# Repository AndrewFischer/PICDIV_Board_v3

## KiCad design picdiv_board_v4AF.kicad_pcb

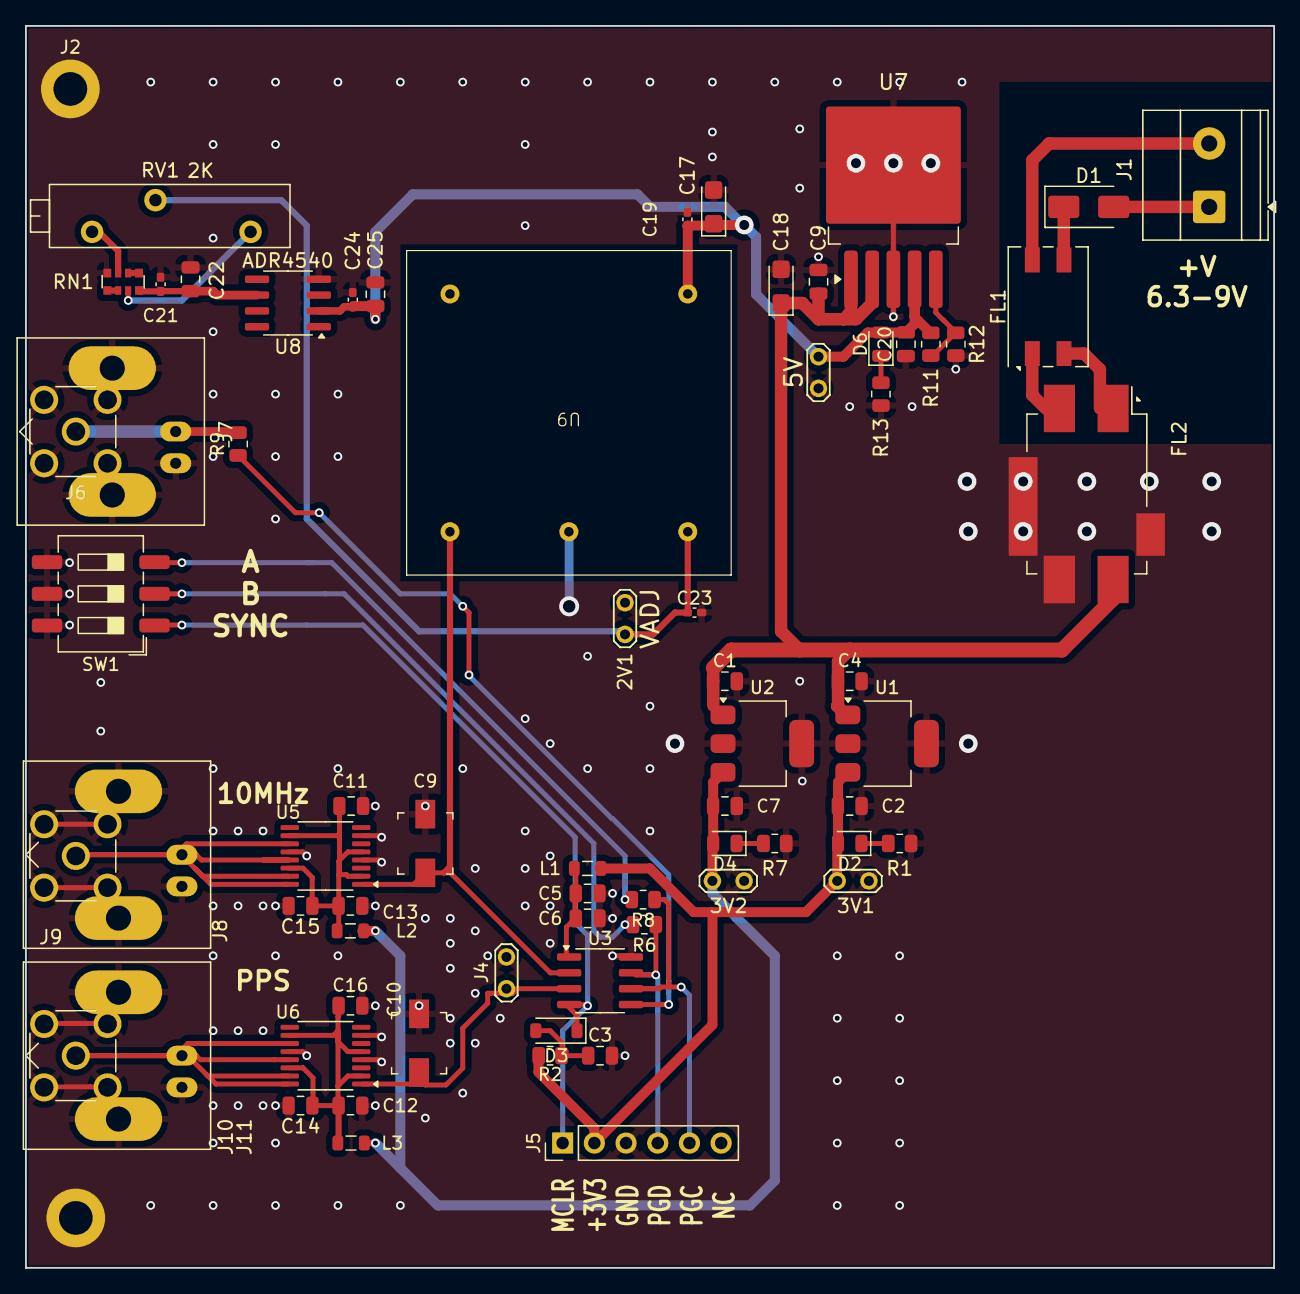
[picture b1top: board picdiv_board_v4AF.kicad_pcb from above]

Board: 2 copper layers, 100.0 x 99.5 mm, 70 parts (0 on the bottom side), 35 nets.

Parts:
2V1: VADJ; TestPoint_2Pads_Pitch2.54mm_Drill0.8mm
3V1, 3V2: TEST_3V3; TestPoint_2Pads_Pitch2.54mm_Drill0.8mm
5V1: 5V; TestPoint_2Pads_Pitch2.54mm_Drill0.8mm
C1, C2, C4, C5, C7, C9: 10u; C_0805_2012Metric
C3, C6, C11, C12, C13, C14, C15, C16: 100n; C_0805_2012Metric
C9#2, C10: C_Trim; C_Trimmer_Murata_TZB4-A
C17, C18: 10µF; CP_EIA-3216-18_Kemet-A
C19, C21, C23, C24: 100nF; C_0402_1005Metric_Pad0.74x0.62mm_HandSolder
C20, C22, C25: 10µF; C_0805_2012Metric
D1: SS34; D_SMA
D2, D4, D6: LED; LED_0805_2012Metric
D3: 1N4148W; D_SOD-123
FL1: Filter_EMI_LL_1423; Filter_Bourns_SRF0905_6.0x9.2mm
FL2: BNX025; Filter_Murata_BNX025
J1: DC-Input; TerminalBlock_Phoenix_MKDS-1,5-2-5.08_1x02_P5.08mm_Horizont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
J2, J3: MountingHole_M2.5; MountingHole_2.7mm_M2.5_DIN965_Pad
J4: TEST_1PPS; TestPoint_2Pads_Pitch2.54mm_Drill0.8mm
J5: Conn_01x06; PinHeader_1x06_P2.54mm_Vertical
J6: Sync; SMA_Molex_73251-2200_Horizontal
J7: Sync; BNC_Amphenol_B6252HB-NPP3G-50_Horizontal
J8: 10MHz; BNC_Amphenol_B6252HB-NPP3G-50_Horizontal
J9: 10MHz; SMA_Molex_73251-2200_Horizontal
J10: PPS_B; BNC_Amphenol_B6252HB-NPP3G-50_Horizontal
J11: PPS_B; SMA_Molex_73251-2200_Horizontal
L1, L2, L3: 2u2; L_0805_2012Metric
R1, R7: 100Ω; R_0805_2012Metric
R2: 3k3; R_0805_2012Metric
R6, R8: 10k; R_0805_2012Metric
R9: 50; R_0805_2012Metric
R11: 2k15; R_0805_2012Metric
R12: 680R; R_0805_2012Metric
R13: 330R; R_0805_2012Metric
RN1: 1K 0.1% ±15ppm; R_Array_Convex_4x0612
RV1: 2K; Potentiometer_Bourns_3006P_Horizontal
SW1: SW_DIP_x03; SW_DIP_SPSTx03_Slide_6.7x9.18mm_W8.61mm_P2.54mm_LowProfile
U1, U2: LT1963AEST-3.3; SOT-223-3_TabPin2
U3: PIC12F675-xSN; SOIC-8_3.9x4.9mm_P1.27mm
U5, U6: IDT5PB1108; TSSOP-16_4.4x5mm_P0.65mm
U7: LT1963AEQ; TO-263-5_TabPin3
U8: ADR4540; SOIC-8_3.9x4.9mm_P1.27mm
U9: OSC5A2B02

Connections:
3V3_OUT: 3V2.1, C7.1, D4.2 (A), L2.2, L3.2, U2.3 (OUT)
3V3_PIC: 3V1.1, C2.1, D2.2 (A), J5.2, L1.2, R2.1, U1.3 (OUT)
10MHz: C9#2.2, U3.2 (GP5), U5.1 (CLKIN), U9.1 (Out)
+5V: 5V1.1, C17.1, C19.1, C20.2, C24.1, C25.1, D6.2 (A), R11.1, U7.4 (OUT), U8.2 (IN), U9.5 (Vcc)
/A: R8.2, SW1.3
/B: R6.2, SW1.2
/PPS_B: J10.1 (In), J11.1 (In), U6.11 (Y5), U6.13 (Y2), U6.15 (Y3), U6.16 (Y1)
/U6_3V3: C12.1, C14.1, C16.1, L3.1, U6.2 (1G), U6.5 (VDD), U6.10 (VDD), U6.14 (VDD)
/U105_3V3: C11.1, C13.1, C15.1, L2.1, U5.2 (1G), U5.5 (VDD), U5.10 (VDD), U5.14 (VDD)
/sync: R9.1, U3.5 (GP2)
/w1: D1.2 (A), J1.1
/w2: D1.1 (K), FL1.3
/w3: FL1.2, FL2.1 (B)
/w4: FL1.4, J1.2
/w5: FL1.1, FL2.3 (PSG)
GND: 2V1.2, 3V1.2, 3V2.2, 5V1.2, C1.2, C2.2, C3.2, C4.2, C5.2, C6.2, C7.2, C9.2, C9#2.1, C10.2, C11.2, C12.2, C13.2, C14.2, C15.2, C16.2, C17.2, C18.2, C19.2, C20.1, C21.2, C22.2, C23.2, C24.2, C25.2, FL2.4 (CG), J2.1, J3.1, J4.2, J5.3, J6.2 (Ext), J7.2 (Ext), J8.2 (Ext), J9.2 (Ext), J10.2 (Ext), J11.2 (Ext), R1.1, R7.1, R12.2, R13.2, RN1.4 (R4.1), SW1.4, SW1.5, SW1.6, U1.2 (GND), U2.2 (GND), U3.8 (VSS), U5.4 (GND), U5.7 (GND), U5.12 (GND), U6.4 (GND), U6.7 (GND), U6.12 (GND), U7.3 (GND), U8.4 (GND), U9.2 (GND)
LDO_IN: C1.1, C4.1, C9.1, C18.1, FL2.2 (CB), U1.1 (IN), U2.1 (IN), U7.1 (~SHDN), U7.2 (IN)
MCLR: D3.1 (K), J5.1, SW1.1, U3.4 (GP3)
unnamed: D2.1 (K), R1.2
unnamed: C3.1, D3.2 (A), R2.2
unnamed: D4.1 (K), R7.2
unnamed: D6.1 (K), R13.1
unnamed: J6.1 (In), J7.1 (In), R9.2
unnamed: J8.1 (In), J9.1 (In), U5.11 (Y5), U5.13 (Y2), U5.15 (Y3), U5.16 (Y1)
unnamed: RN1.1 (R1.1), RN1.2 (R2.1)
unnamed: C21.1, C22.1, RN1.8 (R1.2), U8.6 (OUT)
unnamed: RN1.7 (R2.2), RV1.1
unnamed: RN1.3 (R3.1), RV1.3
unnamed: RN1.5 (R4.2), RN1.6 (R3.2)
unnamed: C5.1, C6.1, L1.1, U3.1 (VDD)
unnamed: R11.2, R12.1, U7.5 (ADJ)
PGC: J5.5, R8.1, U3.6 (GP1)
PGD: J5.4, R6.1, U3.7 (GP0)
PPS: C10.1, J4.1, U3.3 (GP4), U6.1 (CLKIN)
Vadj: 2V1.1, C23.1, RV1.2, U9.3 (Vref)

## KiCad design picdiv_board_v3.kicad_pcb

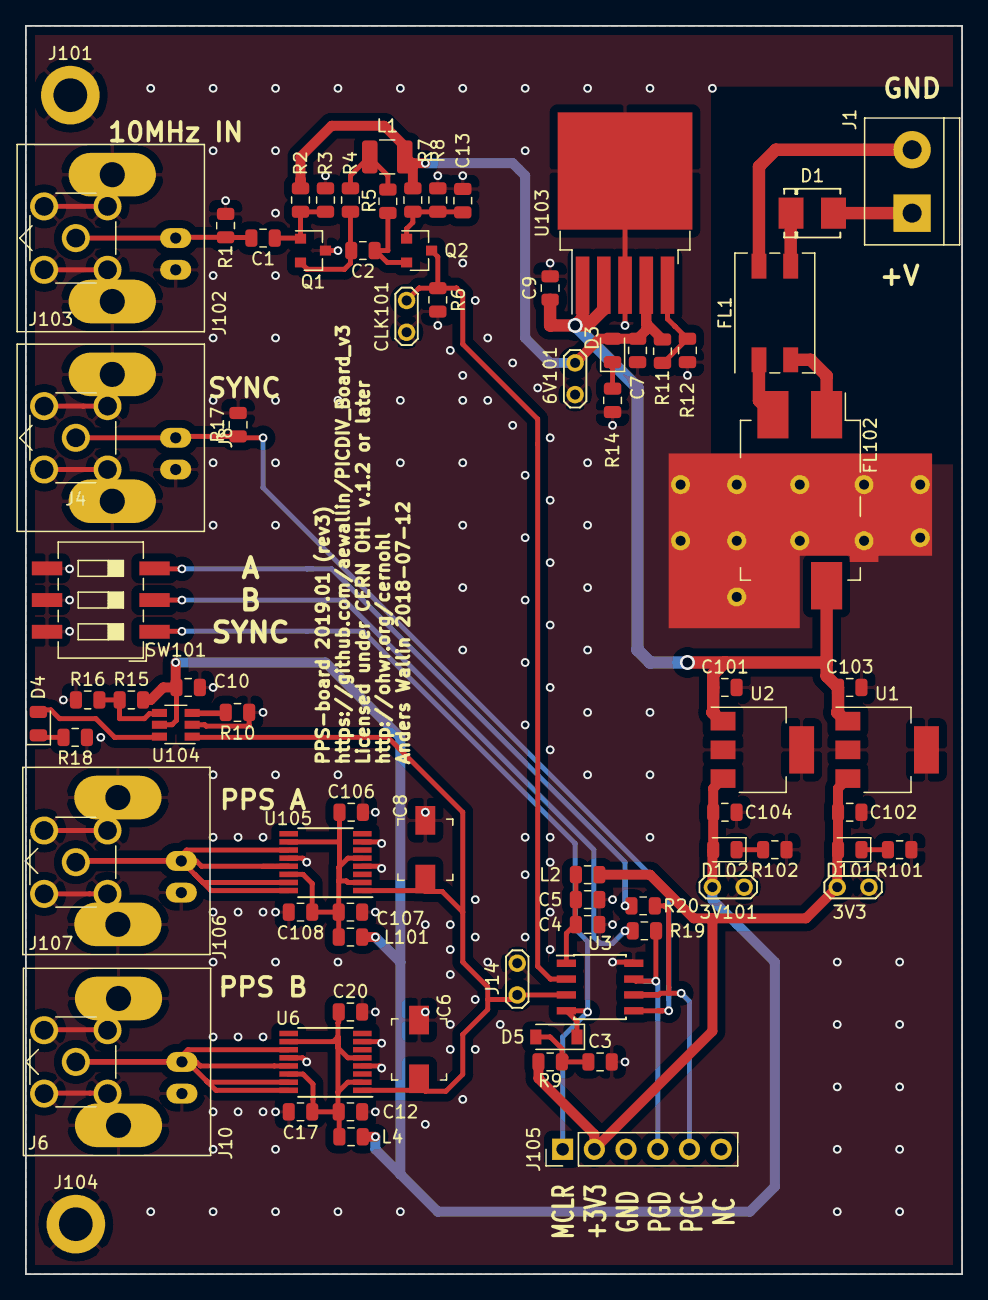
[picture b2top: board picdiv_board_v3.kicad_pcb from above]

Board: 2 copper layers, 75.0 x 100.0 mm, 81 parts (0 on the bottom side), 38 nets.

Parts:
3V3, 3V101: TEST_3V3; TestPoint_2Pads_Pitch2.54mm_Drill0.8mm
6V101: TEST_6V; TestPoint_2Pads_Pitch2.54mm_Drill0.8mm
C1, C13: 10n; C_0805_2012Metric
C2, C4, C12, C17, C20, C106, C107, C108: 100n; C_0805_2012Metric
C3, C10: C; C_0805_2012Metric
C5, C7, C9, C101, C102, C103, C104: 10u; C_0805_2012Metric
C6, C8: C_Trim; C_Trimmer_Murata_TZB4-A
CLK101: TEST_CLK; TestPoint_2Pads_Pitch2.54mm_Drill0.8mm
D1: D; DIODE_DO-214BA
D3, D101, D102: LED; LED_0805_2012Metric
D4: PPS_BLINK; LED_0805_2012Metric
D5: 1N4148; D_SOD-123
FL1: Filter_EMI_LL_1423; Filter_Bourns_SRF0905_6.0x9.2mm
FL102: BNX025; Filter_Murata_BNX025_ThermalVias
J1: DC-Input; TerminalBlock_bornier-2_P5.08mm
J4: SYNC; SMA_Molex_73251-2200_Horizontal
J6: PPS_B; SMA_Molex_73251-2200_Horizontal
J8: SYNC; BNC_Amphenol_B6252HB-NPP3G-50_Horizontal
J10: PPS_B; BNC_Amphenol_B6252HB-NPP3G-50_Horizontal
J14: TEST_1PPS; TestPoint_2Pads_Pitch2.54mm_Drill0.8mm
J101, J104: MountingHole_M2.5; MountingHole_2.7mm_M2.5_DIN965_Pad
J102: Conn_Coaxial; BNC_Amphenol_B6252HB-NPP3G-50_Horizontal
J103: Conn_Coaxial; SMA_Molex_73251-2200_Horizontal
J105: Conn_01x06; PinHeader_1x06_P2.54mm_Vertical
J106: PPS_A; BNC_Amphenol_B6252HB-NPP3G-50_Horizontal
J107: PPS_A; SMA_Molex_73251-2200_Horizontal
L1: 100u (1210); L_1210_3225Metric
L2, L4, L101: 2u2; L_0805_2012Metric
Q1, Q2: Q_PNP_BEC; SOT-23
R1: 49R9; R_0805_2012Metric
R2, R7, R9: 3k3; R_0805_2012Metric
R3, R8: 6k8; R_0805_2012Metric
R4, R5: 220R; R_0805_2012Metric
R6: 270R; R_0805_2012Metric
R10: 300k; R_0805_2012Metric
R11: 2k7; R_0805_2012Metric
R12: 680R; R_0805_2012Metric
R14: 200R; R_0805_2012Metric
R15: 1M; R_0805_2012Metric
R16: 523k; R_0805_2012Metric
R17: 50R; R_0805_2012Metric
R18: 100R; R_0805_2012Metric
R19, R20: 10k; R_0805_2012Metric
R101, R102: 82R; R_0805_2012Metric
SW101: SW_DIP_x03; SW_DIP_SPSTx03_Slide_6.7x9.18mm_W8.61mm_P2.54mm_LowProfile
U1, U2: LT1963AxST-3.3; SOT-223-3_TabPin2
U3: PIC12F675; SOIC-8_3.9x4.9mm_P1.27mm
U6, U105: IDT5PB1108; TSSOP-16_4.4x5mm_P0.65mm
U103: LT1963AEQ; TO-263-5_TabPin3
U104: LTC6993xS6-1; TSOT-23-6

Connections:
3V3_OUT: 3V101.1, C10.1, C104.1, D102.2, L4.2, L101.2, R15.2, U2.3, U104.5
3V3_PIC: 3V3.1, C102.1, D101.2, J105.2, L2.2, R9.1, U1.3
+6V: 6V101.1, C7.2, D3.2, L1.1, R2.1, R7.1, R11.1, U103.4
/A: R20.2, SW101.3
/B: R19.2, SW101.2
/PPS_A: J106.1, J107.1, U105.11, U105.13, U105.15, U105.16
/PPS_B: J6.1, J10.1, U6.11, U6.13, U6.15, U6.16
/U6_3V3: C12.1, C17.1, C20.1, L4.1, U6.2, U6.5, U6.10, U6.14
/U105_3V3: C106.1, C107.1, C108.1, L101.1, U105.2, U105.5, U105.10, U105.14
/sync: J4.1, J8.1, R17.1, U3.5
/w1: D1.2, J1.1
/w2: D1.1, FL1.3
/w3: FL1.2, FL102.1
/w4: FL1.4, J1.2
/w5: FL1.1, FL102.3
CLK: CLK101.1, Q2.3, R6.1, U3.2
GND: 3V3.2, 3V101.2, 6V101.2, C3.2, C4.2, C5.2, C6.1, C7.1, C8.2, C9.2, C10.2, C12.2, C13.2, C17.2, C20.2, C101.2, C102.2, C103.2, C104.2, C106.2, C107.2, C108.2, CLK101.2, FL102.4, J4.2, J6.2, J8.2, J10.2, J14.2, J101.1, J102.2, J103.2, J104.1, J105.3, J106.2, J107.2, Q1.3, R1.2, R3.2, R6.2, R8.2, R10.1, R12.2, R14.2, R16.1, R17.2, R18.1, R101.1, R102.1, SW101.4, SW101.5, SW101.6, U1.2, U2.2, U3.8, U6.4, U6.7, U6.12, U103.3, U104.2, U105.4, U105.7, U105.12
LDO_IN: C9.1, C101.1, C103.1, FL102.2, U1.1, U2.1, U103.1, U103.2
MCLR: D5.1, J105.1, SW101.1, U3.4
unnamed: C1.1, Q1.1, R2.2, R3.1
unnamed: C1.2, J102.1, J103.1, R1.1
unnamed: C2.1, Q2.2, R5.2
unnamed: C2.2, Q1.2, R4.2
unnamed: C3.1, D5.2, R9.2
unnamed: C4.1, C5.1, L2.1, U3.1
unnamed: C13.1, Q2.1, R7.2, R8.1
unnamed: D3.1, R14.1
unnamed: D4.1, R18.2
unnamed: D4.2, U104.6
unnamed: D101.1, R101.2
unnamed: D102.1, R102.2
unnamed: L1.2, R4.1, R5.1
unnamed: R10.2, U104.3
unnamed: R11.2, R12.1, U103.5
unnamed: R15.1, R16.2, U104.4
PGC: J105.5, R20.1, U3.6
PGD: J105.4, R19.1, U3.7
PPS: C6.2, C8.1, J14.1, U3.3, U6.1, U104.1, U105.1

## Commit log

2024-11-02 Add .gitignore
    Forked -- I'm going to do my own thing. Easiest to just fork it.
2024-11-03 Added a few datasheets
2024-11-05 Add some datasheets
2024-11-05 More datasheets
2024-11-07 More datasheets.
2024-11-07 Rename datasheets
2024-11-08 Add OSC5A2B02 Symbol to local library
2024-11-08 unimportant backupfiles
2024-11-08 Create OCXO footprint
2024-11-11 Fix OSC5A2B02 Footprint
    The initial one was based on an incorrect foot print. Adjust to actual device.
2024-11-18 Ignore Backups
2024-11-19 Remove sine to square converter
    Not needed.
2024-11-19 Remove redundant items.
2024-11-19 5.0V LDO for OXCO.
2024-11-19 Add sheet for OXCO circuit
    Putting the OXCO portion on a second sheet makes the schematic more better.
2024-11-20 OXCO VRef bits
2024-11-21 More OXCO circuit work
2024-11-21 Datasheets
2024-11-21 More Vadj bits
2024-11-21 voltage divider
2024-11-22 OCXO Rev. 0
2024-11-22 Rename to V4
2024-11-23 A few small changes
2024-11-23 ERC fix
2024-11-23 Import V3 PCB. All changes TBD
2024-11-25 LTSpice madness
2024-11-25 simulating
2024-11-25 Placeholder footprint for trimpot
    also fix a typo
2024-11-26 Add missing footprints
2024-11-27 datasheet updates
2024-11-28 Remove backups
2024-11-28 Rename a datasheet
2024-11-28 trimpot footprint
2024-11-28 things
2024-11-30 LTSpice sim of vref
2024-12-01 Unimportant
2024-12-01 A bit of layout work
    Remove sine to square parts from layout. We don't need it.
2024-12-01 More Layout
2024-12-01 More layout
    Appears to be problem with PIC symbol. I think the library changed on me.
2024-12-01 Getting closer on parts placement.
    Fixed a few backwards parts caused by newer libraries. Several are mirrors of what was in the orginal symbol. I wonder if he made his own to make the schematic clearer.
2024-12-02 Cleanup datasheets
    Remove a few. Rename others.
2024-12-02 spicy
2024-12-04 Redraw for clarity. Add LCSC parts.
2024-12-06 Return of sync
    Put sync connector back on the schematic.
2024-12-12 More layout work
    99.5x100 mm board.
    Sync back on the schematic.
    Move some parts to make room for OCXO
2024-12-13 More Layout work
    All parts are "on the board". Added some missing LCSC part numbers. Fixed a few "lost parts" that happened when I updated the original schematic to the current version of KiCad.
2024-12-13 Add .stp file for FL1
    Added manufacturer .stp file for FL1. The footprint is a kicad library part, so I made the change on the schematic.
2024-12-13 Add 3D models
2024-12-13 Fix more orphans
    Fix parts resulting from change to 5V from 6V.
2024-12-14 Add LCSC numbers for some resistors.
2024-12-16 DC Input layout
    Fix keep out area around DC Input. Add vias to FL2 GND. The vias used to be in the foot print, but are no longer there in the current version of KiCad. Easier to keep the library part and add the via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
2024-12-23 Add LCSC part numbers to schematic
2024-12-23 Layout
    Better Vias. Rotate OCXO. Lots of cleanup. Lots more work needed.
2024-12-23 layout
2024-12-25 More layout, mostly around Vadg
2024-12-25 More layout
    Vadj getting closer. Keep out around OCXO
2024-12-26 Hmmm
2024-12-26 Led Blink
    Replace pricey LT monostable with an NE555. No need for an expensive part.
2024-12-27 remove lock file
2024-12-27 555 work
2024-12-27 Add inverter to 555 input.
2025-01-02 555 stuff
2025-01-05 Start fixing JLC design rule violations. There over 100 left.
2025-05-30 Highlight a DRC error
    Needs more work.

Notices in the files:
picdiv_board_v3.kicad_pcb:
Licensed under CERN OHL v.1.2 or later
